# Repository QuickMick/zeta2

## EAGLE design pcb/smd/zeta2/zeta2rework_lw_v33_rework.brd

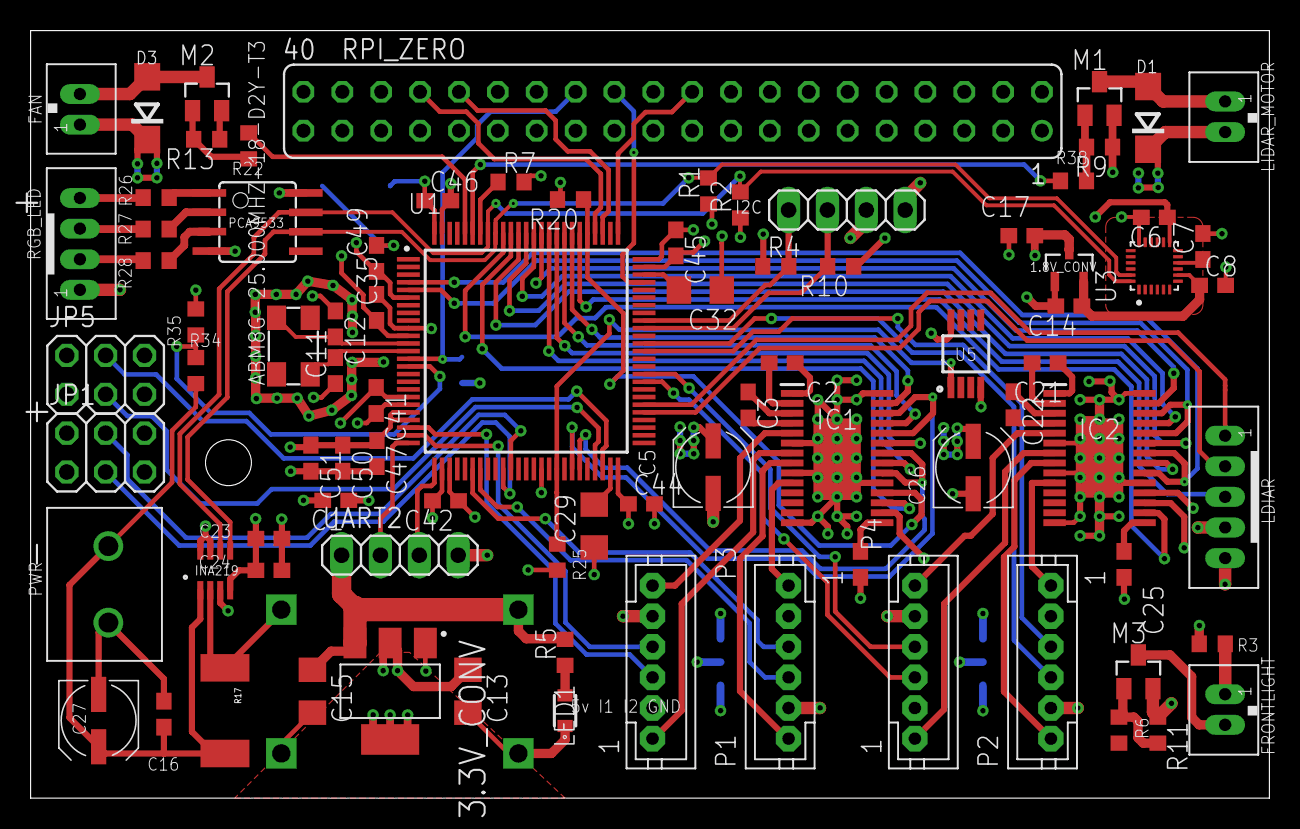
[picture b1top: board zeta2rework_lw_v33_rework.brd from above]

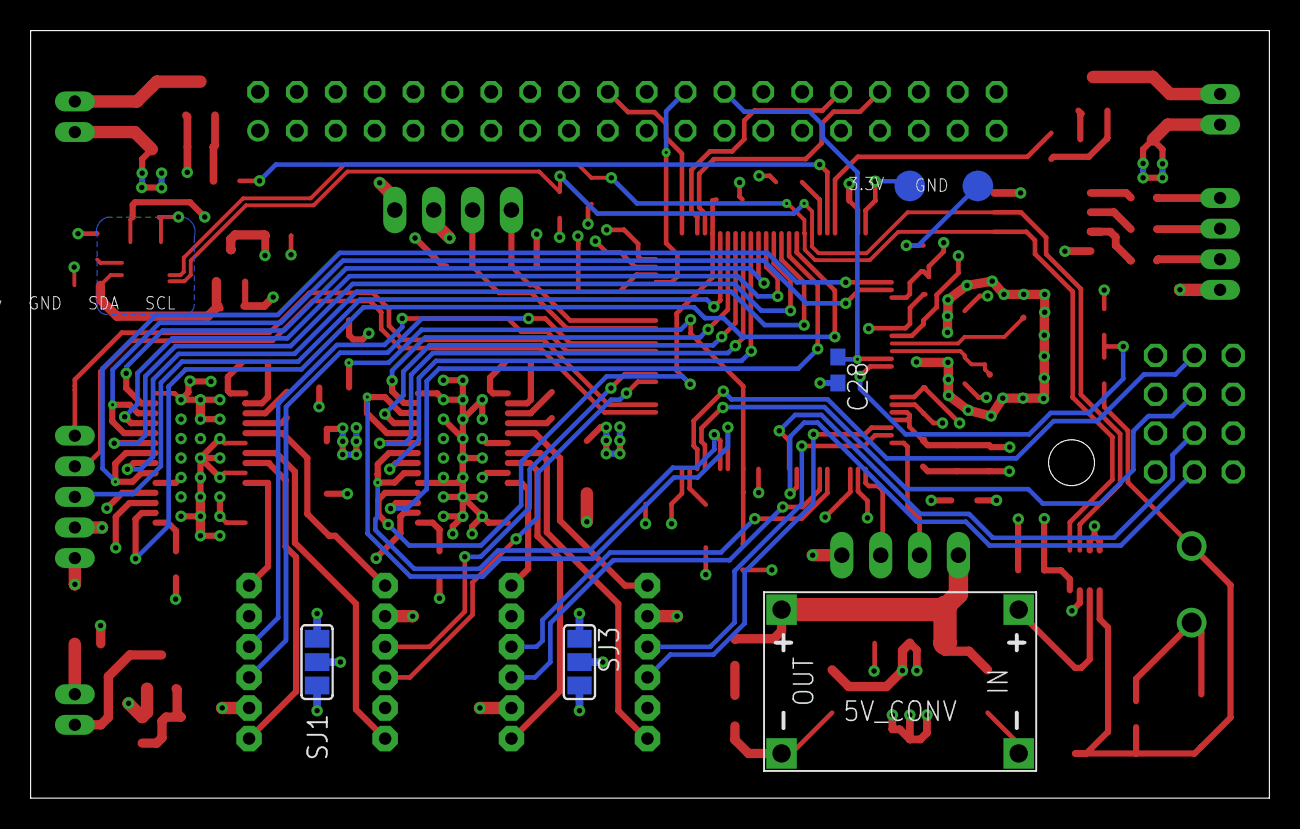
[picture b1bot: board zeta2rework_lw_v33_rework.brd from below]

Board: 4 copper layers, 81.0 x 50.2 mm, 92 parts (6 on the bottom side), 90 nets.

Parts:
1.8V_CONV: MCP1700T-1802E/TT; SOT95P237X112-3N
3.3V: TPSQTP20R; TP20R
3.3V_CONV: NCP1117LPST33T3G; SOT230P700X175-4N
5V_CONV: DC-DC-STEP-DOWN-MP2307
ABM8G-25.000MHZ-18-D2Y-T3: 25mhz; 5.0X3.2_KX-9A
C1: 4.7µf; C0603
C2, C21: 0.01µf 100v; C0603
C3, C22: 0.1µF 16v; C0603
C4, C25: 0.47µF 6.3v; C0603
C5, C26: 47µF; UD-5X5,8_NICHICON
C6, C7, C8: 0.1nF; C0603
C11, C12: Xpf; C0603
C13, C15: 10µF; C1206
C14, C17: 1µF; C0603
C16, C24: 0.1µF; C0603
C23: 100nf; C0603
C27: 100µF; UD-5X5,8_NICHICON
C28, C35, C41, C42, C44, C45, C46, C47, C49, C50: 100nF; C0603
C29, C32: 2.2µf Low ESR < 2ohm; C1206
C51: 1µf; C0603
D1, D3: 1N4004 SMD; DO214AC
FAN: JST-PH_2-PIN_HEADER; JST_B2B-PH_HEADER
FRONTLIGHT: JST-PH_2-PIN_HEADER; JST_B2B-PH_HEADER
GND: TPSQTP20R; TP20R
I2C: 1X04
IC1, IC2: DRV8844PWPR; SOP65P640X120-29N
INA219: INA219; SOT23-8
JP1, JP5: 2X03
LDIAR: JST-PH_5-PIN_HEADER; JST_B5B-PH_HEADER
LED1: LT M673; LTM673-N1R2-25
LIDAR_MOTOR: JST-PH_2-PIN_HEADER; JST_B2B-PH_HEADER
M1, M2, M3: IRLML2502; SOT23
P1, P2, P3, P4: JST-PH6
PCA9533: PCA9533; SOIC8
PWR: 691137710002
R1, R2, R4, R7, R10: 10k; R0603
R3: 0R; R0603
R5, R26, R27, R28: 220R; R0603
R6, R22, R38: 22R; R0603
R9, R11, R13, R20, R34: 100k; R0603
R17: 0.1/1% (PT2512FK-070R1L); 2512
R25: 4k7; R0603
R35: 69k; R0603
RGB_LED: JST-PH_4-PIN_HEADER; JST_B4B-PH_HEADER
RPI_ZERO: FE20-2
SJ1, SJ3: SJ_2
U1: STM32F427VI; QFP50P1600X1600X160-100N
U3: ICM-20948; QFN40P300X300X105-25N
U5: DS18B20U+; SOP65P490X95-8N
UART2: 1X04

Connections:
+1.8V: 1.8V_CONV.2, C8.1, C14.1, U3.8
+3V3: 1.8V_CONV.3, 3.3V.TP, 3.3V_CONV.2, 3.3V_CONV.4, C1.1, C6.1, C13.1, C17.1, C23.1, C24.1, C35.1, C41.1, C42.1, C44.1, C45.1, C46.1, C47.1, C49.1, C50.1, C51.1, INA219.4, PCA9533.8, R1.1, R2.1, R4.1, R10.1, R20.2, R25.2, SJ1.3, SJ3.3, U1.6, U1.11, U1.19, U1.21, U1.22, U1.28, U1.50, U1.75, U1.100, U3.13, U5.8
+5V: 3.3V_CONV.3, 5V_CONV.OUT+, C15.1, I2C.4, JP1.1, JP1.2, JP5.1, JP5.2, LDIAR.P5, R3.1, R5.2, RGB_LED.P1, RPI_ZERO.38, RPI_ZERO.40, SJ1.1, SJ3.1, UART2.1
+8V: 5V_CONV.IN+, C3.2, C5.+, C22.2, C26.+, D1.C, D3.C, FAN.P1, IC1.4, IC1.11, IC2.4, IC2.11, INA219.2, LIDAR_MOTOR.P2, R17.1
BAT_LVL: R34.1, R35.2, U1.15
DEC_LB_1: P1.3, U1.31
DEC_LB_2: P1.4, U1.32
DEC_LF_1: P3.3, U1.23
DEC_LF_2: P3.4, U1.24
DEC_RB_1: P2.3, U1.63
DEC_RB_2: P2.4, U1.64
DEC_RF_1: P4.3, U1.59
DEC_RF_2: P4.4, U1.60
GND: 1.8V_CONV.1, 3.3V_CONV.1, 5V_CONV.IN-, 5V_CONV.OUT-, C1.2, C4.2, C5.-, C6.2, C7.2, C8.2, C11.1, C12.1, C13.2, C14.2, C15.2, C16.2, C17.2, C23.2, C24.2, C25.2, C26.-, C27.-, C28.2, C29.1, C32.1, C35.2, C41.2, C42.2, C44.2, C45.2, C46.2, C47.2, C49.2, C50.2, C51.2, GND.TP, I2C.3, IC1.6, IC1.9, IC1.14, IC1.19, IC1.28, IC1.29, IC2.6, IC2.9, IC2.14, IC2.19, IC2.28, IC2.29, INA219.3, INA219.7, INA219.8, JP1.5, JP1.6, JP5.5, JP5.6, LDIAR.P4, LED1.1, M1.2, M2.2, M3.2, P1.5, P2.5, P3.5, P4.5, PCA9533.4, PWR.2, R7.2, R9.1, R11.1, R13.1, R35.1, RPI_ZERO.1, RPI_ZERO.8, RPI_ZERO.12, RPI_ZERO.15, RPI_ZERO.22, RPI_ZERO.28, RPI_ZERO.31, RPI_ZERO.36, U1.10, U1.20, U1.27, U1.74, U1.99, U3.18, U5.4, UART2.4
I2C1_SCL: INA219.5, PCA9533.6, R1.2, U1.92, U3.23
I2C1_SDA: INA219.6, PCA9533.7, R2.2, U1.93, U3.24
I2C3_SCL: I2C.1, R4.2, U1.67
I2C3_SDA: I2C.2, R10.2, U1.66
LIDAR_POS_INT: LDIAR.P3, U1.81
M_LB_IN1: IC1.23, U1.84
M_LB_IN2: IC1.21, U1.85
M_LF_IN1: IC1.27, U1.82
M_LF_IN2: IC1.25, U1.83
M_PWM_LB: IC1.20, IC1.22, U1.45
M_PWM_LF: IC1.24, IC1.26, U1.44
M_PWM_RB: IC2.20, IC2.22, U1.4
M_PWM_RF: IC2.24, IC2.26, U1.5
M_RB_IN1: IC2.23, U1.88
M_RB_IN2: IC2.21, U1.89
M_RESET: IC1.16, IC2.16, U1.91
M_RF_IN1: IC2.27, U1.86
M_RF_IN2: IC2.25, U1.87
M_SLEEP: IC1.17, IC2.17, U1.90
unnamed: C21.2, IC2.2
unnamed: C21.1, IC2.1
unnamed: C22.1, IC2.3
unnamed: IC2.10, P2.1
unnamed: FRONTLIGHT.P1, R3.2
unnamed: LED1.2, R5.1
unnamed: C7.1, U3.10
unnamed: FRONTLIGHT.P2, M3.3
unnamed: M3.1, R6.2, R11.2
unnamed: IC2.5, P4.6
unnamed: IC2.7, P4.1
unnamed: ABM8G-25.000MHZ-18-D2Y-T3.1, C11.2, U1.13
unnamed: IC1.5, P3.6
unnamed: R7.1, U1.94
unnamed: C2.2, IC1.2
unnamed: IC2.8, P2.6
unnamed: C2.1, IC1.1
unnamed: C3.1, IC1.3
unnamed: PCA9533.1, R26.1
unnamed: PCA9533.2, R27.1
unnamed: PCA9533.3, R28.1
unnamed: C25.1, IC2.15
unnamed: IC1.7, P3.1
unnamed: IC1.8, P1.6
unnamed: C4.1, IC1.15
unnamed: IC1.10, P1.1
unnamed: R26.2, RGB_LED.P4
unnamed: P2.2, P4.2, SJ1.2
unnamed: R27.2, RGB_LED.P3
unnamed: R28.2, RGB_LED.P2
unnamed: C29.2, U1.49
unnamed: M2.1, R13.2, R22.2
unnamed: M1.1, R9.2, R38.2
unnamed: D1.A, LIDAR_MOTOR.P1, M1.3
unnamed: P1.2, P3.2, SJ3.2
unnamed: ABM8G-25.000MHZ-18-D2Y-T3.3, C12.2, U1.12
unnamed: C32.2, U1.73
unnamed: D3.A, FAN.P2, M2.3
NFAULT: IC1.18, IC2.18, R20.1, U1.80
NRST: C28.1, RPI_ZERO.26, U1.14
PWM1: JP5.3, U1.47
PWM2: JP5.4, U1.48
PWM3: JP1.3, U1.35
PWM4: JP1.4, U1.36
PWM_FAN: R22.1, U1.96
PWM_LIDAR: R38.1, U1.95
PWM_LIGHT: R6.1, U1.40
SWCLK: RPI_ZERO.20, U1.76
SWDIO: RPI_ZERO.24, U1.72
TEMPERATURE: R25.1, U1.42, U5.1
UART2_RX: U1.26, UART2.3
UART2_TX: U1.25, UART2.2
UART3_RX: LDIAR.P1, U1.56
UART3_TX: LDIAR.P2, U1.55
UART4_RX: RPI_ZERO.34, U1.79
UART4_TX: RPI_ZERO.32, U1.78
V+: C16.1, C27.+, INA219.1, PWR.1, R17.2, R34.2

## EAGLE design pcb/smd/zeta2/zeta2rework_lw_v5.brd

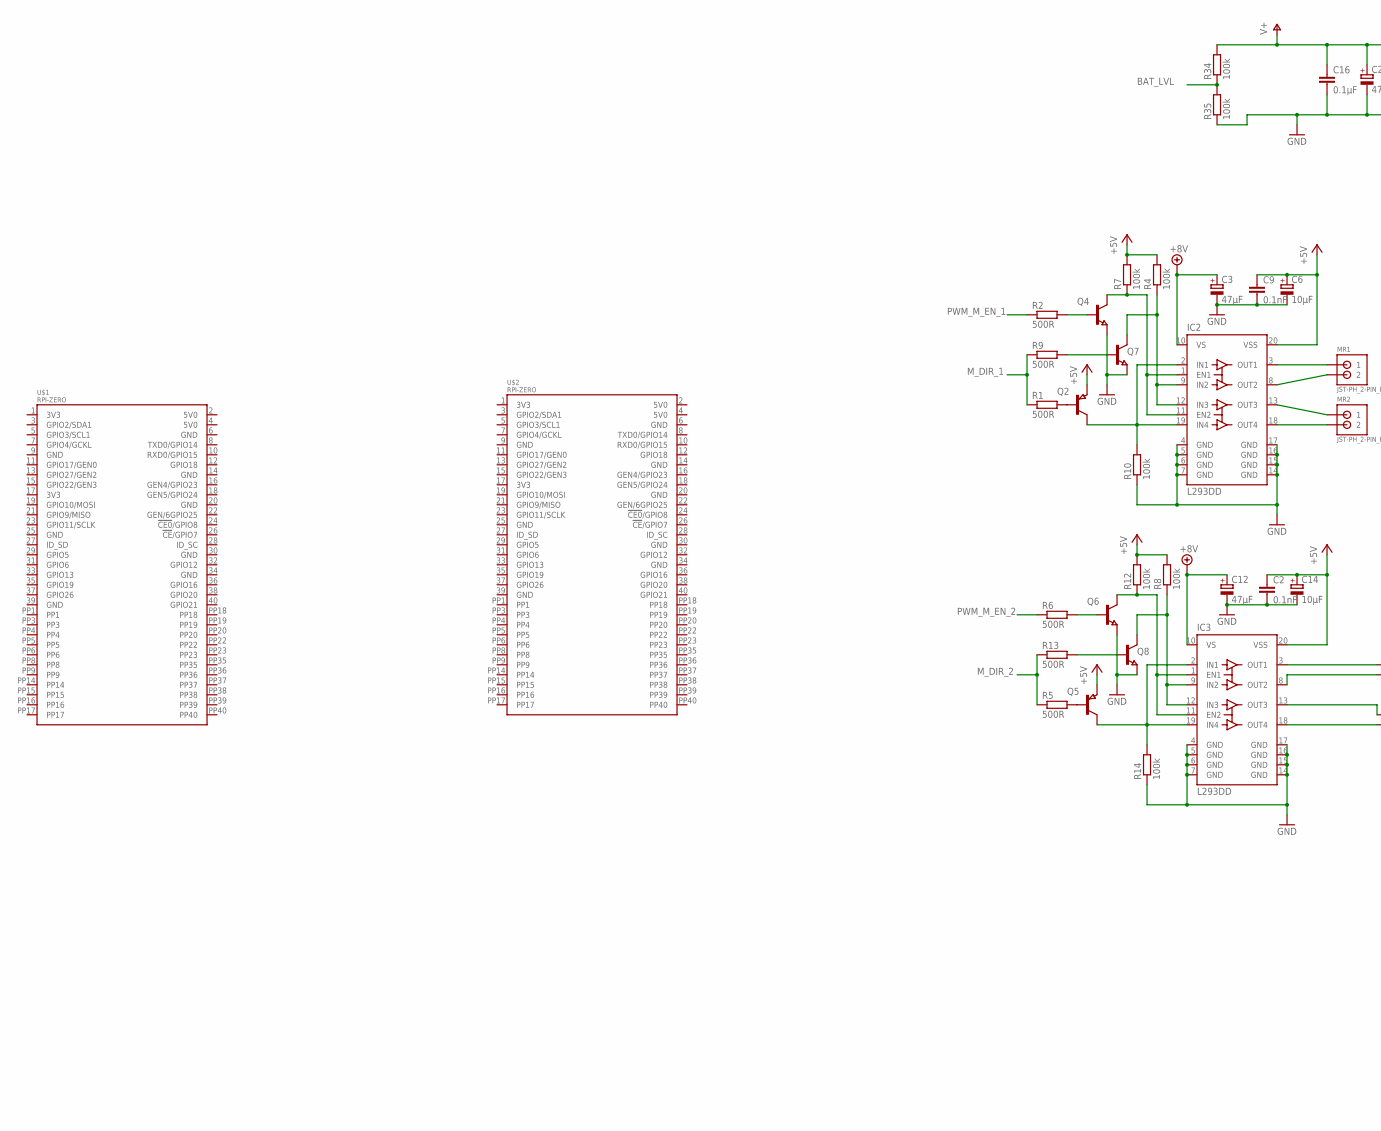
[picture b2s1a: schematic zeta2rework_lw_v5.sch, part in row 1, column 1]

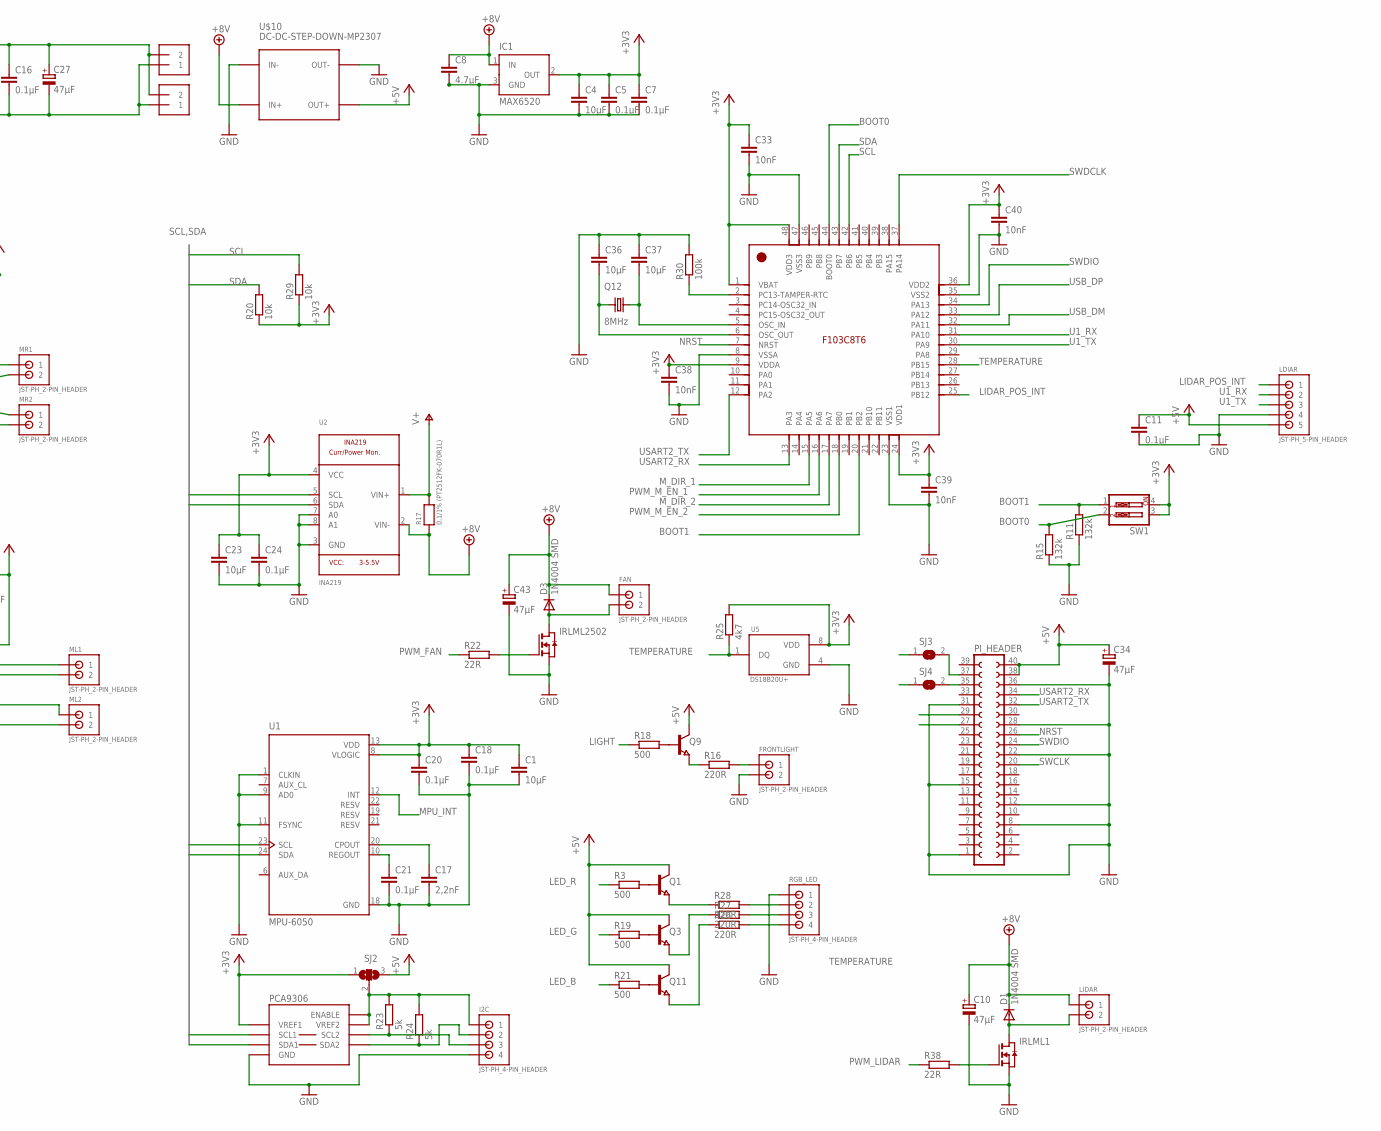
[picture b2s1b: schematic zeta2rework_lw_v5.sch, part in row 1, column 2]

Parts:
C1, C4, C23, C36, C37: 10µF; C1206
C2, C9: 0.1nF; C1206
C3, C10, C12, C27, C34, C43: 47µF; UD-4X5,8_NICHICON
C5, C7, C11, C16, C18, C20, C21, C24: 0.1µF; C1206
C6, C14: 10µF; UD-4X5,8_NICHICON
C8: 4.7µF; C1206
C17: 2,2nF; C1206
C33, C38, C39, C40: 10nF; C1206
D1, D3: 1N4004 SMD; DO214AC
FAN: JST-PH_2-PIN_HEADER; JST_B2B-PH_HEADER
FRONTLIGHT: JST-PH_2-PIN_HEADER; JST_B2B-PH_HEADER
I2C: JST-PH_4-PIN_HEADER; JST_B4B-PH_HEADER
IC1: MAX6520; SOT23
IC2, IC3: L293DD; SO20
IRLML1, IRLML2502: NMOSSOT23; SOT-23
LDIAR: JST-PH_5-PIN_HEADER; JST_B5B-PH_HEADER
LIDAR: JST-PH_2-PIN_HEADER; JST_B2B-PH_HEADER
ML1, ML2: JST-PH_2-PIN_HEADER; JST_B2B-PH_HEADER
MR1, MR2: JST-PH_2-PIN_HEADER; JST_B2B-PH_HEADER
PCA9306: IC2_LEVEL_TRANSLATER; SOIC-8
PI_HEADER: FE20-2
Q1, Q3, Q4, Q6, Q7, Q8, Q9, Q11: NPN-TRANSISTOR_SOT23; SOT23
Q2, Q5: PNP-TRANSISTOR_SOT23; SOT23
Q12: 8MHz; 7.0X5.0
R1, R2, R5, R6, R9, R13: 500R; R0603
R3, R19, R21: 500; R0603
R4, R7, R8, R10, R12, R14, R30, R34, R35: 100k; R0603
R11, R15: 132k; R0603
R16, R26, R27, R28: 220R; R0603
R17: 0.1/1% (PT2512FK-070R1L); 2512
R18: 500; R1206
R20, R29: 10k; R0603
R22, R38: 22R; R0603
R23, R24: 5k; R0603
R25: 4k7; R0603
RGB_LED: JST-PH_4-PIN_HEADER; JST_B4B-PH_HEADER
SJ2: SJ2W; SJ_2
SJ3, SJ4: SOLDERJUMPERREFLOW_NOPASTE; SOLDERJUMPER_REFLOW_NOPASTE
STM32F103CB: STM32F103CB; LQFP48_7X7MM_0.5MMPP
SUPPLY_IN, SUPPLY_IN1: TERMBLOCK_1X2-3.5MM; 1X2-3.5MM
SW1: SW_DIP-2; EDG-02
U1: MPU-6050; QFN50P400X400X95-24N
U2: INA219; SOT23-8
U5: DS18B20U+; SOP65P490X95-8N
U$1, U$2: RPI-ZERO; RASP_PI_ZERO_BOARD_FULL
U$10: DC-DC-STEP-DOWN-MP2307

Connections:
+3V3: C1.1, C4.1, C5.1, C7.1, C18.1, C20.1, C23.1, C24.1, C33.1, C38.1, C39.1, C40.1, IC1.2 (OUT), PCA9306.1 (VREF1), R20.1, R25.2, R29.1, SJ2.1, STM32F103CB.1 (VBAT), STM32F103CB.9 (VDDA), STM32F103CB.24 (VDD1), STM32F103CB.36 (VDD2), STM32F103CB.48 (VDD3), SW1.3, SW1.4, U1.8 (VLOGIC), U1.13 (VDD), U2.4 (VCC), U5.8 (VDD)
+5V: C2.1, C6.+, C9.1, C11.1, C14.+, C34.+, IC2.20 (VSS), IC3.20 (VSS), LDIAR.P5 (5), PI_HEADER.38, PI_HEADER.40, Q1.3 (C), Q2.2 (E), Q3.3 (C), Q5.2 (E), Q9.3 (C), Q11.3 (C), R4.2, R7.2, R8.2, R12.2, SJ2.3, U$10.OUT+
+8V: C3.+, C8.1, C10.+, C12.+, C43.+, D1.C, D3.C, FAN.P1 (1), IC1.1 (IN), IC2.10 (VS), IC3.10 (VS), LIDAR.P1 (1), R17.1, U2.2 (VIN-), U$10.IN+
BAT_LVL: R34.1, R35.2
BOOT0: R15.2, STM32F103CB.44 (BOOT0), SW1.2
BOOT1: R11.2, STM32F103CB.20 (PB2), SW1.1
BOOT2: PI_HEADER.29
BOOT3: PI_HEADER.27
GND: C1.2, C2.2, C3.-, C4.2, C5.2, C6.-, C7.2, C8.2, C9.2, C10.-, C11.2, C12.-, C14.-, C16.2, C17.2, C18.2, C20.2, C21.2, C23.2, C24.2, C27.-, C33.2, C34.-, C36.1, C37.1, C38.2, C39.2, C40.2, C43.-, FRONTLIGHT.P2 (2), I2C.P4 (4), IC1.3 (GND), IC2.4 (GND), IC2.5 (GND), IC2.6 (GND), IC2.7 (GND), IC2.14 (GND), IC2.15 (GND), IC2.16 (GND), IC2.17 (GND), IC3.4 (GND), IC3.5 (GND), IC3.6 (GND), IC3.7 (GND), IC3.14 (GND), IC3.15 (GND), IC3.16 (GND), IC3.17 (GND), IRLML1.2 (S), IRLML2502.2 (S), LDIAR.P4 (4), PCA9306.4 (GND), PI_HEADER.1, PI_HEADER.8, PI_HEADER.12, PI_HEADER.15, PI_HEADER.22, PI_HEADER.28, PI_HEADER.31, PI_HEADER.36, Q4.2 (E), Q6.2 (E), Q7.2 (E), Q8.2 (E), R10.1, R11.1, R14.1, R15.1, R30.2, R35.1, RGB_LED.P1 (1), STM32F103CB.8 (VSSA), STM32F103CB.23 (VSS1), STM32F103CB.35 (VSS2), STM32F103CB.47 (VSS3), SUPPLY_IN.1, SUPPLY_IN1.1, U1.1 (CLKIN), U1.9 (AD0), U1.11 (FSYNC), U1.18 (GND), U2.3 (GND), U2.7 (A0), U2.8 (A1), U5.4 (GND), U$10.IN-, U$10.OUT-
LED_B: R21.1
LED_G: R19.1
LED_R: R3.1
LIDAR_POS_INT: LDIAR.P1 (1), STM32F103CB.25 (PB12)
LIGHT: R18.1
MPU_INT: U1.12 (INT)
M_DIR_1: R1.1, R9.1, STM32F103CB.15 (PA5)
M_DIR_2: R5.1, R13.1, STM32F103CB.17 (PA7)
unnamed: IC2.9 (IN2), IC2.12 (IN3), Q7.3 (C), R4.1
unnamed: IC3.18 (OUT4), ML2.P2 (2)
unnamed: IC3.13 (OUT3), ML2.P1 (1)
unnamed: IC2.18 (OUT4), MR2.P2 (2)
unnamed: IC2.2 (IN1), IC2.19 (IN4), Q2.3 (C), R10.2
unnamed: IC3.9 (IN2), IC3.12 (IN3), Q8.3 (C), R8.1
unnamed: IC3.2 (IN1), IC3.19 (IN4), Q5.3 (C), R14.2
unnamed: IC2.1 (EN1), IC2.11 (EN2), Q4.3 (C), R7.1
unnamed: IC3.1 (EN1), IC3.11 (EN2), Q6.3 (C), R12.1
unnamed: Q2.1 (B), R1.2
unnamed: Q4.1 (B), R2.2
unnamed: Q7.1 (B), R9.2
unnamed: Q5.1 (B), R5.2
unnamed: Q6.1 (B), R6.2
unnamed: Q8.1 (B), R13.2
unnamed: IC2.13 (OUT3), MR2.P1 (1)
unnamed: IC2.8 (OUT2), MR1.P2 (2)
unnamed: IC2.3 (OUT1), MR1.P1 (1)
unnamed: Q9.1 (B), R18.2
unnamed: Q9.2 (E), R16.1
unnamed: FRONTLIGHT.P1 (1), R16.2
unnamed: Q1.1 (B), R3.2
unnamed: Q3.1 (B), R19.2
unnamed: Q1.2 (E), R28.1
unnamed: IC3.8 (OUT2), ML1.P2 (2)
unnamed: IC3.3 (OUT1), ML1.P1 (1)
unnamed: Q3.2 (E), R27.1
unnamed: Q11.2 (E), R26.1
unnamed: R26.2, RGB_LED.P4 (4)
unnamed: Q11.1 (B), R21.2
unnamed: R27.2, RGB_LED.P3 (3)
unnamed: C17.1, U1.20 (CPOUT)
unnamed: R28.2, RGB_LED.P2 (2)
unnamed: C21.1, U1.10 (REGOUT)
unnamed: IRLML2502.3 (G), R22.2
unnamed: IRLML1.3 (G), R38.2
unnamed: D1.A, IRLML1.1 (D), LIDAR.P2 (2)
unnamed: I2C.P1 (1), PCA9306.7 (VREF2), PCA9306.8 (ENABLE), R23.2, R24.2, SJ2.2
unnamed: I2C.P3 (3), PCA9306.6 (SCL2), R23.1
unnamed: I2C.P2 (2), PCA9306.5 (SDA2), R24.1
unnamed: PI_HEADER.37, SJ3.2
unnamed: PI_HEADER.35, SJ4.2
unnamed: C36.2, Q12.1, STM32F103CB.6 (OSC_OUT)
unnamed: C37.2, Q12.3 (2), STM32F103CB.5 (OSC_IN)
unnamed: R30.1, STM32F103CB.2 (PC13-TAMPER-RTC)
unnamed: D3.A, FAN.P2 (2), IRLML2502.1 (D)
NRST: PI_HEADER.26, STM32F103CB.7 (NRST)
PWM_FAN: R22.1
PWM_LIDAR: R38.1
PWM_M_EN_1: R2.1, STM32F103CB.16 (PA6)
PWM_M_EN_2: R6.1, STM32F103CB.18 (PB0)
SCL: R29.2, STM32F103CB.42 (PB6), U1.23 (SCL), U2.5 (SCL)
SCL2: PCA9306.2 (SCL1)
SCL3: SJ4.1
SDA: R20.2, STM32F103CB.43 (PB7), U1.24 (SDA), U2.6 (SDA)
SDA2: PCA9306.3 (SDA1)
SDA3: SJ3.1
SWCLK: PI_HEADER.20
SWDCLK: STM32F103CB.37 (PA14)
SWDIO: PI_HEADER.24, STM32F103CB.34 (PA13)
TEMPERATURE: R25.1, STM32F103CB.28 (PB15), U5.1 (DQ)
U1_RX: LDIAR.P2 (2), STM32F103CB.31 (PA10)
U1_TX: LDIAR.P3 (3), STM32F103CB.30 (PA9)
USART2_RX: PI_HEADER.34, STM32F103CB.13 (PA3)
USART2_TX: PI_HEADER.32, STM32F103CB.12 (PA2)
USB_DM: STM32F103CB.32 (PA11)
USB_DP: STM32F103CB.33 (PA12)
V+: C16.1, C27.+, R17.2, R34.2, SUPPLY_IN.2, SUPPLY_IN1.2, U2.1 (VIN+)

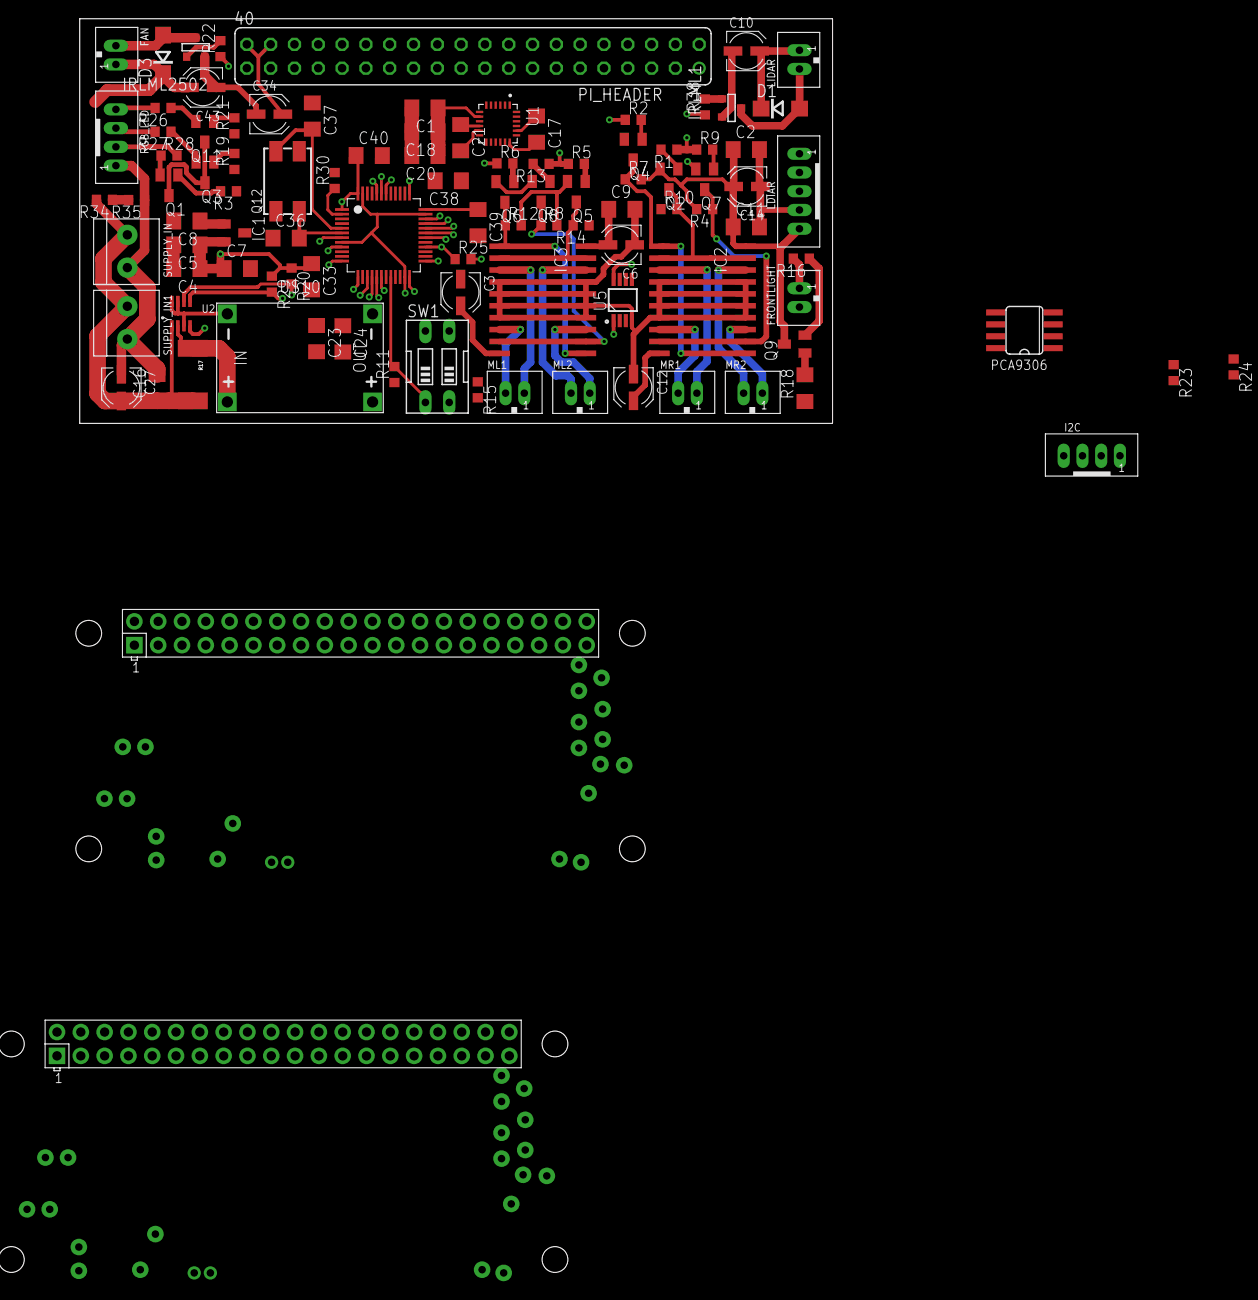
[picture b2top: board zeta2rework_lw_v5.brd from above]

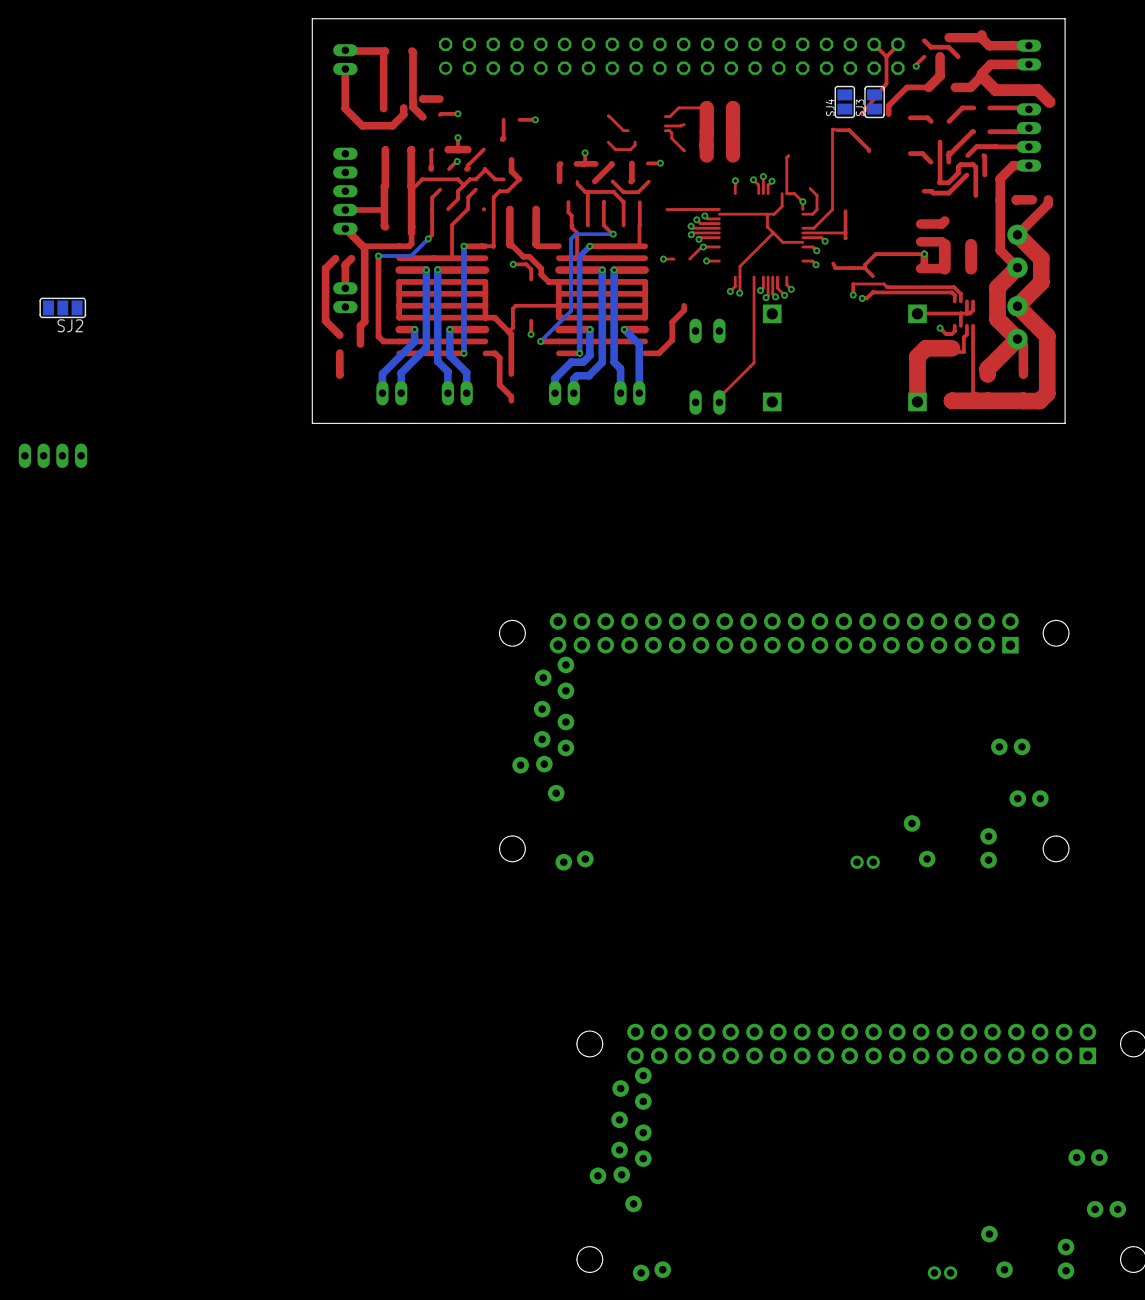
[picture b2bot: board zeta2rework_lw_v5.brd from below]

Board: 2 copper layers, 80.3 x 43.2 mm, 105 parts (3 on the bottom side), 68 nets.

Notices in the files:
parts and their libraries:
diy-modules: Released under the Creative Commons Attribution 4.0 International License: http://creativecommons.org/licenses/by/4.0
crystal-geyer_V1_0: Copyright: Geyer-Electronic
